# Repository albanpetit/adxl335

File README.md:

# ADXL335

Here is the repository of one of my electronic projects, a rather simple electronic card around a MEMS accelerometer : ADXL335. MEMS accelerometers are compact devices that exploit microfabrication technology to integrate mechanical elements, sensors, actuators, and electronics on a tiny silicon chip. At the core of these devices lies a MEMS structure, often composed of microstructures such as beams or cantilevers, which respond to external forces.

This entire project is documented on my [personal website](https://albanpetit.com/posts/adxl-335-accelerometer/), from the electronic card to the code necessary for its operation, including its manufacturing itself. 

## Project structure and usage

Project structure :
- **ecad** : ecad kicad source files, gerber and ibom
- **mcad** : mechanical part of the project, using Fusion360 older than : v.2.0.18477
- **firware** : Arduino script, any version of the programming work, no extra library needed

This project use the latest at this date version of kicad : 8.0.2. 

## Contribution

If you're interested in contributing, i'd love to have your input. Here's how you can get started:

1. **Fork the Repository:** Click on the "Fork" button at the top right of this repository to create your own copy.
2. **Clone Your Fork:** Clone your forked repository to your local machine using the following command:
   ```bash
   git clone https://github.com/albanpetit/adxl335
   ```
3. **Create a New Branch:** Switch to a new branch for your contributions.
   ```bash
   git checkout -b feature/your-feature-name
   ```
4. **Make Changes:** Make the necessary changes or additions to improve the website.
5. **Commit Your Changes:** Commit your changes with descriptive commit messages.
   ```bash
   git commit -m "feat: description of the new feature"
   ```
6. **Push to Your Fork:** Push your changes to your forked repository.
   ```bash
   git push origin feature/your-feature-name
   ```
7. **Open a Pull Request:** Once you've pushed your changes to your fork, open a pull request in our repository. Provide a detailed description of your changes and any relevant information.

### Commit naming convention

To make the commit history as readable as possible, I try to adhere as closely as I can to the following naming convention :

```
<type> <sujet>

<description>
```

- **Type** defines the type of commit
  - **git**: gitignore modification. submodule update, merging
  - **docs**: Documentation
  - **feat**: Add firmware feature
  - **fix**: Bug fix on firmware
  - **perf**: Code performance improvement
  - **ecad**: Electronic Computer Aided Design
  - **mcad**: Mechanical Computer Aided Design
  - **refactor**: Code changement which does not change the usage
- **Sujet** contains a brief description of the changes
  Using the present imperative ("change", not "changed" or "changes")
  Without capital letter at the beginning
  No "." at the end of the description
- **Description** allows to detail in more detail the motivations behind
  the change. The rules are the same as for the Subject part.

I invite you to follow this convention to contribute more easily to this repository.

### Feedback and Issues

If you encounter any issues, have suggestions, or want to discuss new features,
please open an issue on the GitHub repository. Your feedback is highly valued!

Thank you for considering contributing.

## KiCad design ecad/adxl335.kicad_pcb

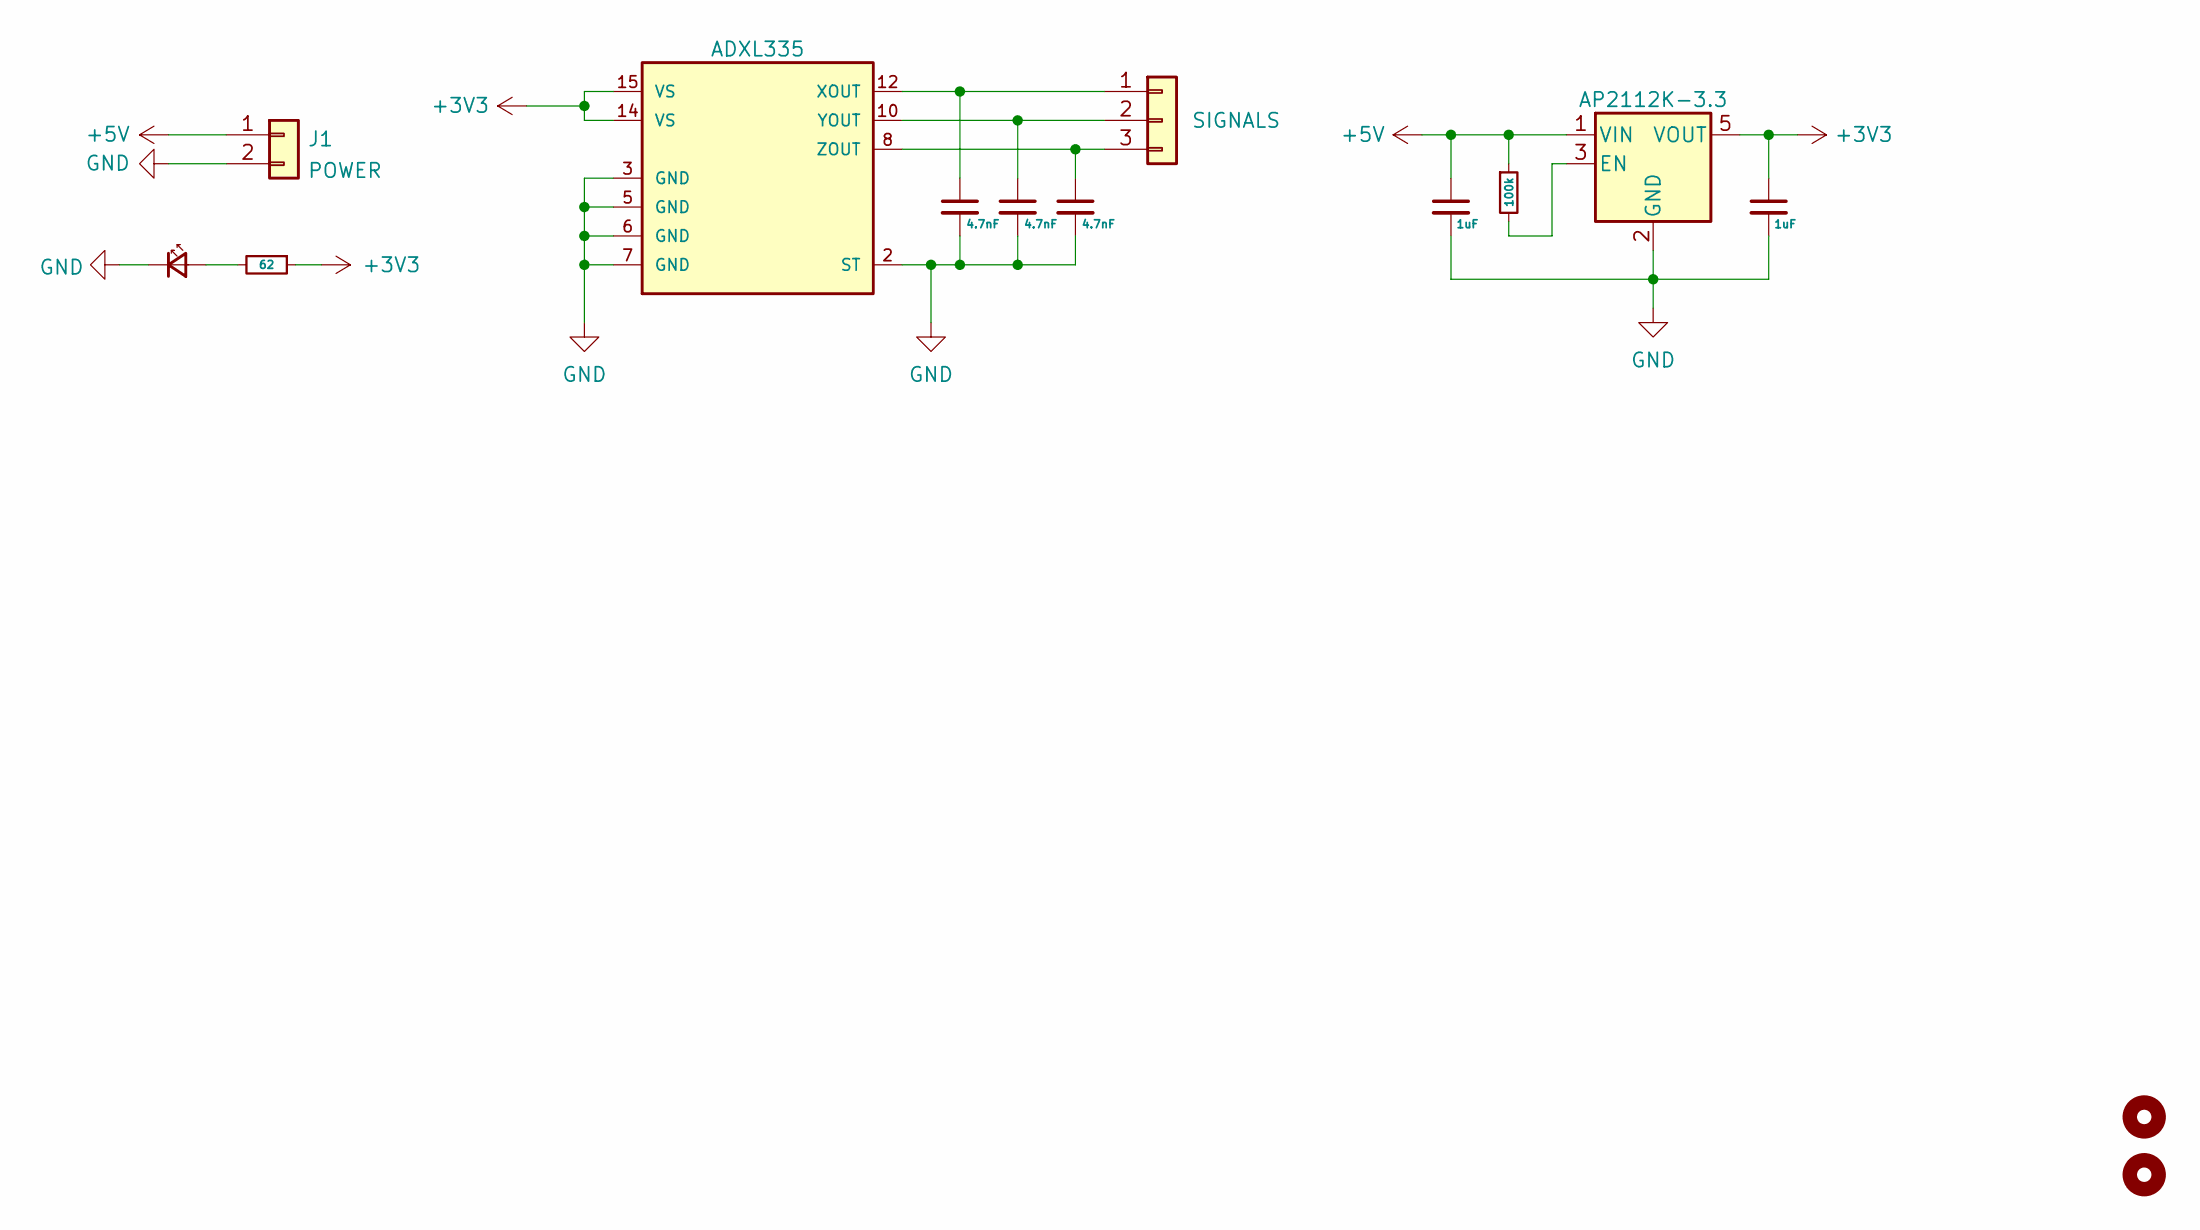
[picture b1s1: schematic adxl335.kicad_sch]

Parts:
C1, C2, C3: 4.7nF; C_0603_1608Metric
C4, C5: 1uF; C_0603_1608Metric
D1: POWER; LED_0603_1608Metric
H3, H4: MountingHole; MountingHole_2.2mm_M2_DIN965_Pad
J1: POWER; JST_PH_B2B-PH-SM4-TB_1x02-1MP_P2.00mm_Vertical
J2: SIGNALS; JST_PH_B3B-PH-SM4-TB_1x03-1MP_P2.00mm_Vertical
R1: 62; R_0603_1608Metric
R2: 100k; R_0603_1608Metric
U1: ADXL335; LFCSP-16
U2: AP2112K-3.3; SOT-23-5

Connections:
+3V3: C5.1, R1.1, U1.14 (VS), U1.15 (VS), U2.5 (VOUT)
+5V: C4.1, J1.1, R2.1, U2.1 (VIN)
GND: C1.2, C2.2, C3.2, C4.2, C5.2, D1.1 (K), J1.2, U1.2 (ST), U1.3 (GND), U1.5 (GND), U1.6 (GND), U1.7 (GND), U2.2 (GND)
unnamed: D1.2 (A), R1.2
unnamed: C1.1, J2.1, U1.12 (XOUT)
unnamed: C2.1, J2.2, U1.10 (YOUT)
unnamed: C3.1, J2.3, U1.8 (ZOUT)
unnamed: R2.2, U2.3 (EN)

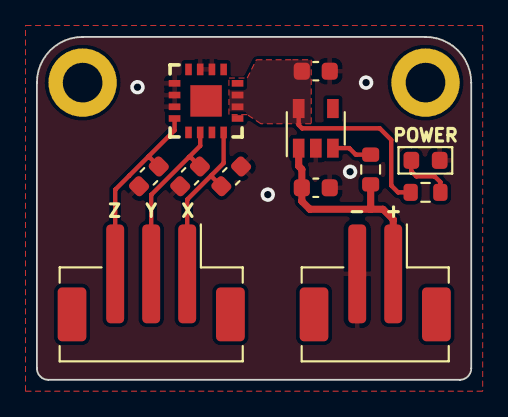
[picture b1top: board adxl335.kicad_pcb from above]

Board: 2 copper layers, 24.1 x 19.1 mm, 14 parts (0 on the bottom side), 8 nets.

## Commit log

2024-05-08 git: add gitignore
2024-05-08 docs: init readme
2024-05-08 feat: add arduino code to read acceleration
2024-05-08 feat: initial commit
2024-05-08 git: remove log files
2024-05-08 git: add kicad_sch lck files to gitignore
2024-05-17 docs: start readme documentation
2024-05-17 docs: readme image and contribution process
2024-05-17 docs: refactor list in commit naming convention
2024-05-20 fix: remove gerber zip
2024-05-20 docs: more project information in README
